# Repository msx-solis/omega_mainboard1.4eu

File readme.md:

# omega_mainboard1.4eu
This is a variant from the OMEGA HOME COMPUTER mainboard pcb 1.4us.
Is based on the last design for the mainboard pcb (version 1.4us). You can find it at https://github.com/skiselev/omega
Please, refer to it for full documentation or you can also go to https://msxmakers.design.blog/proyectos/omega-home-computer/

## changes
The only changes from mainboard version 1.4us are:

a) Din-8 connectors used are more common on EU than in 1.4us version.

b) the jumpers for selecting the mapper changes are not connected so a cutout of the traces is not needed.

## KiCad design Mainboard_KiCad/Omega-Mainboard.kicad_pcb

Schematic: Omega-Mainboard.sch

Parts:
HOLE1, HOLE2, HOLE3, HOLE4, HOLE5, HOLE6, HOLE7, HOLE8, HOLE9, HOLE10, HOLE11: HOLE; Hole_3mm
J1: 5V; Conn_Power_Jack_Circular_Pads
J10: POWER; Conn_Friction_Lock_8P_2.54mm

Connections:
VDD: J10.7; also elsewhere on the board
VSS: J10.8; also elsewhere on the board

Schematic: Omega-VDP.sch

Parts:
C51, C52, C53, C54, C55, C56: 0.1uF; Cap_Cer_508
C59, C60, C61, C62, C63, C64: 220uF; Cap_Elec_Radial_10mm
C77: 10uF; Cap_Elec_Radial_5mm
C82, C83, C84: 330pF; Cap_Cer_508
C85: 47pF; Cap_Cer_508
C89, C90: 30pF; C_Trim_Murata
C91: 27pF; Cap_Cer_508
C92, C93: 22pF; Cap_Cer_508
C94: 4.7pF; Cap_Cer_508
J2: Composite; Conn_RCA_Right
J4: S-VIDEO; Conn_Mini_DIN_4pin
J5: RGB; DIN8
J14: CBUS; Conn_Pin_Header_13x1_2.54mm
JP3, JP4: V9938/V9958; Conn_Pin_Header_3x1_2.54mm
JP5, JP6: NTSC/PAL; Conn_Pin_Header_3x1_2.54mm
L1: 68uH; Res_762
Q2: PN2907A; Transistor_TO92_EBC_254
R1: 1M; Res_762
R2: 470k; Res_762
R7: 47k; Res_762
R9: 20k; Res_762
R14: 10k; Res_762
R25: 2.2k; Res_762
R27, R28, R30, R33: 1k; Res_762
R35: 180; Res_762
R36: 120; Res_762
R37, R38, R39, R40: 100; Res_762
R43, R44, R45, R46, R47, R48: 75; Res_762
RR2, RR3: 10k; Conn_SIL10
RR9: 470; Conn_SIL6
U3: V9938/V9958; IC_SDIP64_600
U8, U9, U10, U11: D41464; IC_DIP18_300
U39: 74AHCT32; IC_DIP14_300
U43: 74HCT04; IC_DIP14_300
U47: CXA1645; IC_DIP24_400
Y1: 21.477270MHz; Crystal_HC-49U_Vert
Y3: 4.433618MHz; Crystal_HC-49U_Vert

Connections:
/A0: U3.29 (MODE0); also elsewhere on the board
/A1: U3.28 (MODE1); also elsewhere on the board
/AUDIO: J5.2; also elsewhere on the board
/CLK: U3.8 (CPUCLK), U39.4, U39.5; also elsewhere on the board
/D0: U3.40 (CD0); also elsewhere on the board
/D1: U3.39 (CD1); also elsewhere on the board
/D2: U3.38 (CD2); also elsewhere on the board
/D3: U3.37 (CD3); also elsewhere on the board
/D4: U3.36 (CD4); also elsewhere on the board
/D5: U3.35 (CD5); also elsewhere on the board
/D6: U3.34 (CD6); also elsewhere on the board
/D7: U3.32 (CD7); also elsewhere on the board
/VDP/AV: J5.3, R14.2, R33.1
/VDP/BLUE: C53.1, C84.1, RR9.6, U3.24 (B)
/VDP/BOUT: C64.2, J5.8
/VDP/CB0: J14.12, RR2.6, U3.19 (C0)
/VDP/CB1: J14.11, RR2.5, U3.18 (C1)
/VDP/CB2: J14.10, RR2.4, U3.17 (C2)
/VDP/CB3: J14.9, RR2.3, U3.16 (C3)
/VDP/CB4: J14.8, RR2.2, U3.15 (C4)
/VDP/CB5: J14.7, RR3.10, U3.14 (C5)
/VDP/CB6: J14.6, RR3.9, U3.13 (C6)
/VDP/CB7: J14.5, RR3.8, U3.12 (C7)
/VDP/CBDR: J14.4, U3.11 (CBDR)
/VDP/CHROMA: C60.2, J4.4
/VDP/COMP: C59.2, J2.1, J5.4
/VDP/CSYNC: R27.2, U3.6 (CSYNC)
/VDP/GOUT: C63.2, J5.7
/VDP/GREEN: C52.1, C83.1, RR9.4, U3.22 (G)
/VDP/HSYNC: RR9.2, U3.5 (HSYNC)
/VDP/LUMA: C61.2, J4.3
/VDP/PAL_CLK: JP6.3, U43.4
/VDP/RED: C51.1, C82.1, RR9.5, U3.23 (R)
/VDP/ROUT: C62.2, J5.6
/VDP/SYNCIN: C85.1, JP4.2, U47.10 (SYNCIN)
/VDP/VA0: U3.49 (AD0), U8.14 (A0), U9.14 (A0), U10.14 (A0), U11.14 (A0)
/VDP/VA1: U3.50 (AD1), U8.13 (A1), U9.13 (A1), U10.13 (A1), U11.13 (A1)
/VDP/VA2: U3.51 (AD2), U8.12 (A2), U9.12 (A2), U10.12 (A2), U11.12 (A2)
/VDP/VA3: U3.52 (AD3), U8.11 (A3), U9.11 (A3), U10.11 (A3), U11.11 (A3)
/VDP/VA4: U3.53 (AD4), U8.8 (A4), U9.8 (A4), U10.8 (A4), U11.8 (A4)
/VDP/VA5: U3.54 (AD5), U8.7 (A5), U9.7 (A5), U10.7 (A5), U11.7 (A5)
/VDP/VA6: U3.55 (AD6), U8.6 (A6), U9.6 (A6), U10.6 (A6), U11.6 (A6)
/VDP/VA7: U3.56 (AD7), U8.10 (A7), U9.10 (A7), U10.10 (A7), U11.10 (A7)
/VDP/VD0: U3.41 (RD0), U8.2 (D1), U10.2 (D1)
/VDP/VD1: U3.42 (RD1), U8.3 (D2), U10.3 (D2)
/VDP/VD2: U3.43 (RD2), U8.15 (D3), U10.15 (D3)
/VDP/VD3: U3.44 (RD3), U8.17 (D4), U10.17 (D4)
/VDP/VD4: U3.45 (RD4), U9.2 (D1), U11.2 (D1)
/VDP/VD5: U3.46 (RD5), U9.3 (D2), U11.3 (D2)
/VDP/VD6: U3.47 (RD6), U9.15 (D3), U11.15 (D3)
/VDP/VD7: U3.48 (RD7), U9.17 (D4), U11.17 (D4)
/VDP/VIDEO: JP3.2, U3.21 (VIDEO)
/VDP/YS: J5.5, R35.2, R36.1
/VDP/~CAS0: R38.1, U8.16 (~CAS), U9.16 (~CAS)
/VDP/~CAS1: R39.1, U10.16 (~CAS), U11.16 (~CAS)
/VDP/~DHCLK: J14.2, RR3.2, U3.2 (~DHCLK)
/VDP/~DLCLK: J14.3, RR3.3, U3.3 (~DLCKL)
/VDP/~RAS: R40.1, U8.5 (~RAS), U9.5 (~RAS), U10.5 (~RAS), U11.5 (~RAS)
/VDP/~VDP_RD: U3.31 (~CSR), U39.3
/VDP/~VDP_WR: U3.30 (~CSW), U39.11
/VDP/~VWR: R37.1, U8.4 (~WE), U9.4 (~WE), U10.4 (~WE), U11.4 (~WE)
/~PSG_CS: U39.9; also elsewhere on the board
/~RD: U39.1; also elsewhere on the board
/~RESET: U3.9 (~RESET); also elsewhere on the board
/~VDP_CS: U39.2, U39.13; also elsewhere on the board
/~VDP_INT: RR2.7, U3.25 (~INT); also elsewhere on the board
/~VDP_WAIT: RR2.8, U3.26 (~LPS); also elsewhere on the board
/~WR: U39.12; also elsewhere on the board
unnamed: C51.2, U47.2 (RIN)
unnamed: C52.2, U47.3 (GIN)
unnamed: C53.2, U47.4 (BIN)
unnamed: C54.1, U47.9 (YCLPC)
unnamed: C55.1, R7.1, U47.13 (IREF)
unnamed: C56.2, U3.33 (VBB)
unnamed: C59.1, R43.1
unnamed: C60.1, R44.1
unnamed: C61.1, R45.1
unnamed: C62.1, R46.1
unnamed: C63.1, R47.1
unnamed: C64.1, R48.1
unnamed: C77.1, U47.14 (VREF)
unnamed: C89.2, R2.2, U3.63 (XTAL1), Y1.2
unnamed: C90.2, R30.1, Y3.2
unnamed: C91.1, U47.17 (YTRAP)
unnamed: C91.2, L1.1
unnamed: C92.2, R2.1, U3.64 (XTAL2), Y1.1
unnamed: C93.2, R1.2, U43.1, Y3.1
unnamed: C94.1, R25.1, U47.6 (SCIN)
unnamed: JP3.1, RR9.3
unnamed: JP4.1, U43.6
unnamed: JP4.3, Q2.2, R27.1
unnamed: JP5.2, U47.7 (NTSC/~PAL)
unnamed: JP6.1, U39.6
unnamed: JP6.2, R25.2
unnamed: Q2.3, R28.2, U43.5
unnamed: R1.1, R30.2, U43.2, U43.3
unnamed: R9.1, U47.18 (FO)
unnamed: R37.2, U3.57 (R/~W)
unnamed: R38.2, U3.61 (~CAS0)
unnamed: R39.2, U3.60 (~CAS1)
unnamed: R40.2, U3.62 (~RAS)
unnamed: R43.2, U47.20 (CVOUT)
unnamed: R44.2, U47.15 (COUT)
unnamed: R45.2, U47.16 (YOUT)
unnamed: R46.2, U47.23 (ROUT)
unnamed: R47.2, U47.22 (GOUT)
unnamed: R48.2, U47.21 (BOUT)
unnamed: RR2.9, U3.27 (~LPD)
unnamed: RR3.4, U3.4 (~VDS)
unnamed: RR3.5, U3.59 (~CASX)
unnamed: RR3.6, U3.7 (BLEO)
unnamed: RR3.7, U3.10 (~YS)
unnamed 387: U39.8; also elsewhere on the board
unnamed 388: U39.10; also elsewhere on the board
VCCRGB: JP5.1, U47.12 (VCC), U47.19 (VCC); also elsewhere on the board
VCCVDP: JP3.3, U3.58 (VCC); also elsewhere on the board

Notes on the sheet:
JP3, JP4: 1-2: V9938; 2-3: V9958 (Use a wire link) JP4, JP5: 1-2: NTSC; 2-3: PAL (Use a wire link)
PAL: R9 - 16k, C91 - 18pF R9 - Tolerance 1%
PCB Layout Notes: Keep trace length between CXA1645 and 75 ohm resistors to minimum CXA1645 bypass capacitors: VCC1(12), VREF(14) -> GND1(1), VCC2(19) -> GND2(24)
Optional: PAL Clock Generator
Optional: RGB Output
Install Q2 only for V9938

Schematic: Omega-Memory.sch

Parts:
J12: RAM_EXT; Conn_Pin_Header_20x2_2.54mm
JP1: ROM_A18; Conn_Pin_Header_2x1_2.54mm
JP7, JP8: RAM_SIZE; Conn_Pin_Header_2x3_2.54mm
R13: 10k; Res_762
RR10: 4.7k; Conn_SIL6
U6: SST39SF040; IC_DIP32_600
U7: AS6C4008; IC_DIP32_600
U15, U16, U17, U18: 74HCT670; IC_DIP16_300
U26: 74F245; IC_DIP20_300
U32: 74AHCT138; IC_DIP16_300
U37: 74AHCT32; IC_DIP14_300

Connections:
/A0: J12.31, U6.12 (A0), U7.12 (A0), U15.5, U15.14, U16.5, U16.14, U17.14, U18.14; also elsewhere on the board
/A1: J12.29, U6.11 (A1), U7.11 (A1), U15.4, U15.13, U16.4, U16.13, U17.13, U18.13; also elsewhere on the board
/A2: J12.27, U6.10 (A2), U7.10 (A2); also elsewhere on the board
/A3: J12.25, U6.9 (A3), U7.9 (A3); also elsewhere on the board
/A4: J12.23, U6.8 (A4), U7.8 (A4); also elsewhere on the board
/A5: J12.21, U6.7 (A5), U7.7 (A5); also elsewhere on the board
/A6: J12.19, U6.6 (A6), U7.6 (A6); also elsewhere on the board
/A7: J12.17, U6.5 (A7), U7.5 (A7); also elsewhere on the board
/A8: J12.20, U6.27 (A8), U7.27 (A8); also elsewhere on the board
/A9: J12.22, U6.26 (A9), U7.26 (A9); also elsewhere on the board
/A10: J12.28, U6.23 (A10), U7.23 (A10); also elsewhere on the board
/A11: J12.24, U6.25 (A11), U7.25 (A11); also elsewhere on the board
/A12: J12.15, U6.4 (A12), U7.4 (A12); also elsewhere on the board
/A13: J12.18, U6.28 (A13), U7.28 (A13); also elsewhere on the board
/A14: U6.29 (A14), U17.5, U18.5; also elsewhere on the board
/A15: U6.3 (A15), U17.4, U18.4; also elsewhere on the board
/D0: U16.3, U16.6, U18.3, U26.9; also elsewhere on the board
/D1: U16.2, U16.7, U18.2, U26.8; also elsewhere on the board
/D2: U16.1, U16.9, U18.1, U26.7; also elsewhere on the board
/D3: U16.10, U16.15, U18.15, U26.6; also elsewhere on the board
/D4: U15.3, U15.6, U17.3, U26.5; also elsewhere on the board
/D5: JP8.5, U15.2, U17.2, U26.4; also elsewhere on the board
/D6: JP8.1, U15.15, U17.15, U26.3; also elsewhere on the board
/D7: JP8.3, U15.1, U17.1, U26.2; also elsewhere on the board
/Memory/MD0: J12.33, U6.13 (DQ0), U7.13 (DQ0), U26.11
/Memory/MD1: J12.35, U6.14 (DQ1), U7.14 (DQ1), U26.12
/Memory/MD2: J12.37, U6.15 (DQ2), U7.15 (DQ2), U26.13
/Memory/MD3: J12.38, U6.17 (DQ3), U7.17 (DQ3), U26.14
/Memory/MD4: J12.36, U6.18 (DQ4), U7.18 (DQ4), U26.15
/Memory/MD5: J12.34, U6.19 (DQ5), U7.19 (DQ5), U26.16
/Memory/MD6: J12.32, U6.20 (DQ6), U7.20 (DQ6), U26.17
/Memory/MD7: J12.30, U6.21 (DQ7), U7.21 (DQ7), U26.18
/Memory/RAM_A14: J12.13, U7.3 (A14), U18.6
/Memory/RAM_A15: J12.12, U7.31 (A15), U18.7
/Memory/RAM_A16: J12.11, U7.2 (A16), U18.9
/Memory/RAM_A17: J12.14, U7.30 (A17), U18.10
/Memory/RAM_A18: J12.9, U7.1 (A18), U17.6
/Memory/RAM_A19: JP7.2, U17.7
/Memory/RAM_A20: JP7.4, U17.10
/Memory/RAM_A21: JP7.6, U17.9
/Memory/ROM_A18: JP1.2, R13.1, U6.1 (A18)
/Memory/~PAGE_RD: U15.11, U16.11, U37.3
/Memory/~PAGE_WR: U15.12, U16.12, U17.12, U18.12, U37.11
/Memory/~RAM0_CS: U7.22 (~CE), U32.15
/Memory/~RAM1_CS: J12.4, U32.14
/Memory/~RAM2_CS: J12.3, U32.13
/Memory/~RAM3_CS: J12.6, U32.12
/Memory/~RAM4_CS: J12.5, U32.11
/Memory/~RAM5_CS: J12.8, U32.10
/Memory/~RAM6_CS: J12.7, U32.9
/Memory/~RAM7_CS: J12.10, U32.7
/ROM_A16: U6.2 (A16); also elsewhere on the board
/ROM_A17: U6.30 (A17); also elsewhere on the board
/~MEM_RD: U26.1; also elsewhere on the board
/~PAGE_CS: U37.2, U37.12; also elsewhere on the board
/~RAM_SL: U32.4, U32.5; also elsewhere on the board
/~RD: J12.26, U6.24 (~OE), U7.24 (~OE), U37.1; also elsewhere on the board
/~ROM_CS: U6.22 (~CE); also elsewhere on the board
/~WR: J12.16, U6.31 (~WE), U7.29 (~WE), U37.13; also elsewhere on the board
unnamed: JP7.1, RR10.2, U32.1
unnamed: JP7.3, RR10.3, U32.2
unnamed: JP7.5, RR10.4, U32.3
unnamed: JP8.2, U15.10
unnamed: JP8.4, U15.9
unnamed: JP8.6, U15.7

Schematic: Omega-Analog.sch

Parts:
C1, C2, C3, C4, C6, C7, C8, C9, C10, C11, C12, C13, C14, C15, C16, C17, C18, C19, C20, C21, C22, C23, C24, C25, C26, C27, C28, C29, C30, C31, C32, C33, C34, C35, C36, C37, C38, C39, C40, C41, C42, C43, C44, C45, C46, C47, C48, C49, C50, C57, C58: 0.1uF; Cap_Cer_508
C65, C66, C67: 100uF; Cap_Elec_Radial_6.3mm
C68, C69, C70: 10uF; Cap_Pol_508_3
C71, C72, C73, C74, C75, C76: 10uF; Cap_Elec_Radial_5mm
C78: 1uF; Cap_Elec_Radial_5mm
C79, C80: 22nF; Cap_Cer_508
C81: 1.5nF; Cap_Cer_508
D1: 1N4148; Diode_762
J3: Audio; Conn_RCA_Right
J6: Cassette; DIN8
L2, L3: 5.6uH; Res_762
Q1: PN2907A; Transistor_TO92_EBC_254
R3: 470k; Res_762
R4: 220k; Res_762
R8: 47k; Res_762
R10: 20k; Res_762
R11, R12: 10k; Res_762
R15: 5.6k; Res_762
R16, R17, R18, R19, R20, R21, R22: 4.7k; Res_762
R23, R24: 2.7k; Res_762
R26: 2.2k; Res_762
R31, R32: 1k; Res_762
R41, R42: 100; Res_762
RY1: Relay_5V; Relay_SPDT
U48: MCP6281; IC_DIP8_300
U49: LM311; IC_DIP8_300

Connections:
/AUDIO: C76.2, J3.1, R8.1; also elsewhere on the board
/CAS_IN: R4.2, R32.1, U49.7; also elsewhere on the board
/CAS_MOT: R31.1; also elsewhere on the board
/CAS_OUT: C78.1; also elsewhere on the board
/KEY_CLICK: C73.1; also elsewhere on the board
/PSG_SND: C72.1; also elsewhere on the board
/SLT1_SND: C74.1; also elsewhere on the board
/SLT2_SND: C75.1; also elsewhere on the board
unnamed: C57.1, R21.1, R22.2, U48.3
unnamed: C71.1, R12.2, R20.1, R23.1, R24.1
unnamed: C72.2, R26.2
unnamed: C73.2, R10.2
unnamed: C74.2, R16.2
unnamed: C75.2, R17.2
unnamed: C76.1, R41.2
unnamed: C78.2, R18.1
unnamed: C79.1, R18.2, R19.1
unnamed: C80.1, J6.5
unnamed: C80.2, R11.2
unnamed: C81.1, R10.1, R15.1, R16.1, R17.1, R26.1, U48.2
unnamed: C81.2, R15.2, R41.1, U48.6
unnamed: D1.2, Q1.1, RY1.9
unnamed: J6.4, R19.2, R42.1
unnamed: J6.6, RY1.5, RY1.6
unnamed: J6.7, RY1.10
unnamed: Q1.2, R31.2
unnamed: R3.2, R11.1, R12.1, U49.3 (-)
unnamed: R4.1, R20.2, U49.2 (+)
VCCRGB: C47.1, C50.1, C69.1, L3.2; also elsewhere on the board
VCCVDP: C3.1, C58.1, C70.1, L2.2; also elsewhere on the board
VDD: C66.1; also elsewhere on the board
VSS: C67.2; also elsewhere on the board

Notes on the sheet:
C5: RTC
Optional: Cassete I/O

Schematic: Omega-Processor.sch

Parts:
BT1: CR2032; Battery_Holder_CR2032_Universal
C5: 0.1uF; Cap_Cer_508
C86, C87: 33pF; Cap_Cer_508
C88: 30pF; C_Trim_Murata
J9: PRINTER; Conn_Micro_Ribbon_14F
J13: ~RST~/~NMI; Conn_Pin_Header_2x2_2.54mm
R5, R6: 100k; Res_762
R29: 1k; Res_762
RR1: 10k; Conn_SIL10
RR5: 4.7k; Conn_SIL10
U1: Z84C00; IC_DIP40_600
U5: RP5C01; IC_DIP18_300
U12: ATF16V8B; IC_DIP20_300
U24: 74HCT273; IC_DIP20_300
U27: 74HCT175; IC_DIP16_300
U33: 74AHCT125; IC_DIP14_300
U34, U35: 74HCT74; IC_DIP14_300
U37: 74AHCT32; IC_DIP14_300
U42: 74LS07; IC_DIP14_300
U45: 74HCT00; IC_DIP14_300
U46: ADM691A; IC_DIP16_300
Y2: 32768 Hz; Crystal_32K_Horiz

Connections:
/A0: U1.30 (A0), U12.9 (I8); also elsewhere on the board
/A1: U1.31 (A1); also elsewhere on the board
/A2: U1.32 (A2), U12.8 (I7); also elsewhere on the board
/A3: U1.33 (A3), U12.7 (I6); also elsewhere on the board
/A4: U1.34 (A4), U12.6 (I5); also elsewhere on the board
/A5: U1.35 (A5), U12.5 (I4); also elsewhere on the board
/A6: U1.36 (A6), U12.4 (I3); also elsewhere on the board
/A7: U1.37 (A7), U12.3 (I2); also elsewhere on the board
/A8: U1.38 (A8); also elsewhere on the board
/A9: U1.39 (A9); also elsewhere on the board
/A10: U1.40 (A10); also elsewhere on the board
/A11: U1.1 (A11); also elsewhere on the board
/A12: U1.2 (A12); also elsewhere on the board
/A13: U1.3 (A13); also elsewhere on the board
/A14: U1.4 (A14); also elsewhere on the board
/A15: U1.5 (A15); also elsewhere on the board
/CLK: U35.11 (CLK), U42.5, U42.9; also elsewhere on the board
/D0: RR1.3, U1.14 (D0), U5.11 (D0), U24.17 (D6), U27.5 (D1), U35.2 (D); also elsewhere on the board
/D1: RR1.4, U1.15 (D1), U5.12 (D1), U24.14 (D5), U27.4 (D0), U33.3; also elsewhere on the board
/D2: RR1.5, U1.12 (D2), U5.13 (D2), U24.4 (D1), U27.12 (D2); also elsewhere on the board
/D3: RR1.6, U1.8 (D3), U5.14 (D3), U24.7 (D2), U27.13 (D3); also elsewhere on the board
/D4: RR1.7, U1.7 (D4), U24.13 (D4); also elsewhere on the board
/D5: RR1.8, U1.9 (D5), U24.8 (D3); also elsewhere on the board
/D6: RR1.9, U1.10 (D6), U24.18 (D7); also elsewhere on the board
/D7: RR1.10, U1.13 (D7), U24.3 (D0); also elsewhere on the board
/PRT_BUSY: J9.11, U33.2; also elsewhere on the board
/PSG/JB0: U42.1; also elsewhere on the board
/PSG/JB1: U42.13; also elsewhere on the board
/PSG/JB2: U42.11; also elsewhere on the board
/PSG/JB3: U42.3; also elsewhere on the board
/PSG/~TRG1_A: U42.2; also elsewhere on the board
/PSG/~TRG1_B: U42.12; also elsewhere on the board
/PSG/~TRG2_A: U42.10; also elsewhere on the board
/PSG/~TRG2_B: U42.4; also elsewhere on the board
/Processor/ALARM: RR1.2, U5.15 (~ALARM)
/Processor/PD0: J9.2, U24.16 (Q6)
/Processor/PD1: J9.3, U24.15 (Q5)
/Processor/PD2: J9.4, U24.5 (Q1)
/Processor/PD3: J9.5, U24.6 (Q2)
/Processor/PD4: J9.6, U24.12 (Q4)
/Processor/PD5: J9.7, U24.9 (Q3)
/Processor/PD6: J9.8, U24.19 (Q7)
/Processor/PD7: J9.9, U24.2 (Q0)
/Processor/RTC_VCC: C5.1, U5.2 (CS), U5.18 (VCC), U46.2 (Vout)
/Processor/~BUSREQ: RR5.3, U1.25 (~BUSREQ)
/Processor/~INT: U1.16 (~INT), U45.8
/Processor/~NMI: J13.3, RR5.4, U1.17 (~NMI)
/Processor/~PRT_BSY_RD: U33.1, U37.6
/Processor/~PRT_CMD_CS: U12.13 (I/O7), U37.5, U37.10
/Processor/~PRT_DAT_WR: U12.12 (I/O8), U24.11 (CP)
/Processor/~PRT_STB_WR: U35.3 (CLK), U37.8
/Processor/~RTC_AD_WR: U12.17 (I/O3), U27.9 (CP)
/Processor/~RTC_CS: U12.16 (I/O4), U46.13 (~CE_IN)
/Processor/~RTC_CS_B: U5.1 (~CS), U46.12 (~CE_OUT)
/Processor/~STROBE: J9.1, U35.5 (Q)
/RESET: U46.16 (RESET); also elsewhere on the board
/~BUSDIR1: RR5.7; also elsewhere on the board
/~BUSDIR2: RR5.6; also elsewhere on the board
/~IORQ: U1.20 (~IORQ), U12.2 (I1); also elsewhere on the board
/~KBD_WAIT: RR5.2; also elsewhere on the board
/~M1: U1.27 (~M1), U12.11 (I9/~OE), U34.2 (D); also elsewhere on the board
/~M1_WAIT: U34.5 (Q), U34.12 (D); also elsewhere on the board
/~MREQ: U1.19 (~MREQ); also elsewhere on the board
/~PAGE_CS: U12.15 (I/O5); also elsewhere on the board
/~PPI_CS: U12.14 (I/O6), U45.4; also elsewhere on the board
/~PSG_CS: U12.19 (I/O1); also elsewhere on the board
/~RD: U1.21 (~RD), U5.8 (~RD), U37.4; also elsewhere on the board
/~RESET: J13.1, U1.26 (~RESET), U24.1 (~MR), U27.1 (~MR), U35.4 (~PR), U45.2, U46.15 (~RESET); also elsewhere on the board
/~RFSH: U1.28 (~RFSH); also elsewhere on the board
/~SLT_INT: RR5.9, U45.13; also elsewhere on the board
/~SLT_WAIT: RR5.10; also elsewhere on the board
/~VDP_CS: U12.18 (I/O2); also elsewhere on the board
/~VDP_INT: U45.12; also elsewhere on the board
/~WAIT: U1.24 (~WAIT); also elsewhere on the board
/~WR: U1.22 (~WR), U5.10 (~WR), U12.1 (I/CLK), U37.9; also elsewhere on the board
unnamed: BT1.1, U46.1 (Vbatt)
unnamed: C86.2, R5.1, U5.17 (OSCOUT)
unnamed: C87.2, R5.2, Y2.2
unnamed: C88.2, U5.16 (OSCIN), Y2.1
unnamed: R6.1, U5.3 (ADJ)
unnamed: R29.2, U1.6 (CLK), U34.3 (CLK), U34.11 (CLK), U42.8
unnamed 330: U42.6; also elsewhere on the board
unnamed: U5.5 (A1), U27.2 (Q0)
unnamed: U5.4 (A0), U27.7 (Q1)
unnamed: U5.6 (A2), U27.10 (Q2)
unnamed: U5.7 (A3), U27.15 (Q3)
unnamed 370: U45.3, U45.5; also elsewhere on the board
unnamed: U34.4 (~PR), U34.9 (Q)
unnamed 378: U35.9 (Q); also elsewhere on the board
unnamed: U35.8 (~Q), U35.12 (D)
unnamed: U45.1, U45.6
unnamed: U45.9, U45.10, U45.11

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
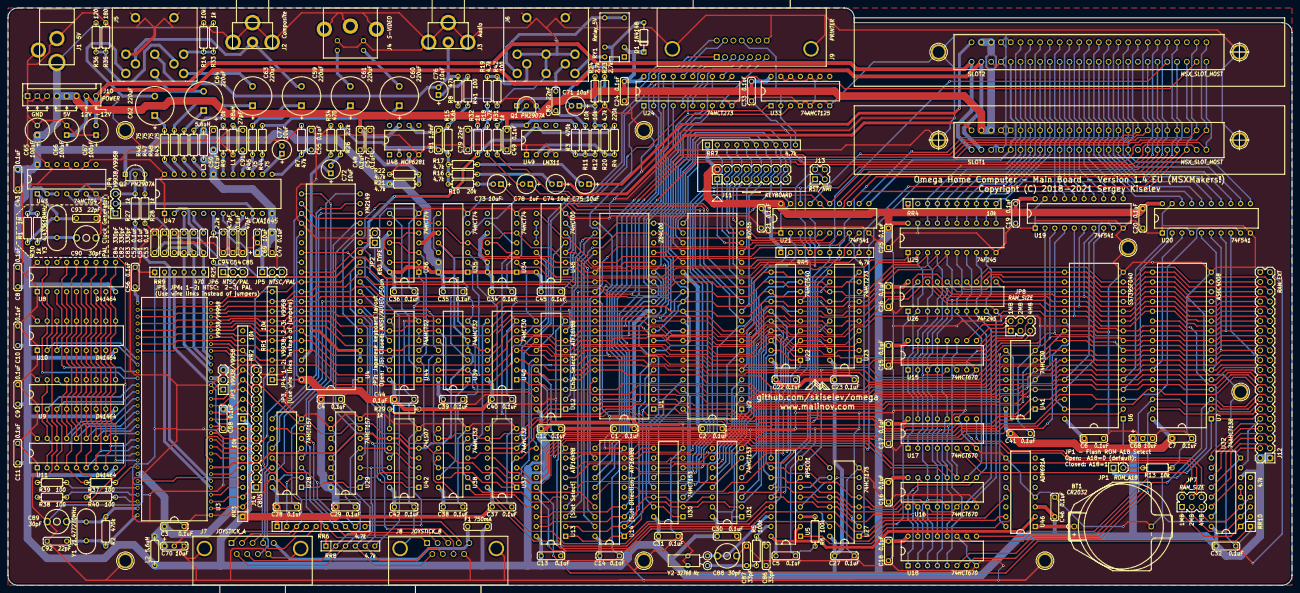
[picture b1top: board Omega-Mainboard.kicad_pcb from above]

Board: 2 copper layers, 333.4 x 149.9 mm, 248 parts (0 on the bottom side), 363 nets.

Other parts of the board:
F1: 750mA; Cap_Cer_508
J7: JOYSTICK_A; Conn_Dsub_DE9M
J8: JOYSTICK_B; Conn_Dsub_DE9M
J11: KEYBOARD; Conn_Pin_Header_8x2_2.54mm
JP2: KBD_TYPE; Conn_Pin_Header_2x1_2.54mm
R34: 470; Res_762
RR4: 10k; Conn_SIL10
RR6, RR7: 4.7k; Conn_SIL10
RR8: 4.7k; Conn_SIL6
SLOT1, SLOT2: MSX_SLOT_HOST; Conn_Edge_50P
U2: 82C55; IC_DIP40_600
U4: YM2149; IC_DIP40_600
U13, U14: ATF16V8B; IC_DIP20_300
U19, U20, U21: 74F541; IC_DIP20_300
U22: 74HCT540; IC_DIP20_300
U23: 74HCT273; IC_DIP20_300
U25: 74F245; IC_DIP20_300
U28, U29: 74HCT157; IC_DIP16_300
U30, U31: 74HCT153; IC_DIP16_300
U36: 74HCT74; IC_DIP14_300
U38: 74AHCT32; IC_DIP14_300
U40, U41: 74HCT30; IC_DIP14_300
U44: 74AHCT02; IC_DIP14_300

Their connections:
/A0: U2.9, U19.7, U40.12, U44.9; also elsewhere on the board
/A1: U2.8, U19.6, U40.11, U44.11; also elsewhere on the board
/A2: U19.5, U40.6; also elsewhere on the board
/A3: U19.4, U40.5; also elsewhere on the board
/A4: U19.3, U40.4; also elsewhere on the board
/A5: U19.2, U40.3; also elsewhere on the board
/A6: U20.5, U40.2; also elsewhere on the board
/A7: U20.4, U40.1; also elsewhere on the board
/A8: U20.3, U41.11; also elsewhere on the board
/A9: U20.8, U41.5; also elsewhere on the board
/A10: U20.7, U41.4; also elsewhere on the board
/A11: U20.6, U41.6; also elsewhere on the board
/A12: U20.2, U41.3; also elsewhere on the board
/A13: U19.9, U41.12; also elsewhere on the board
/A14: U13.2, U14.2, U19.8, U30.14, U31.14, U41.2; also elsewhere on the board
/A15: U13.1, U14.1, U20.9, U30.2, U31.2, U41.1; also elsewhere on the board
/CAS_IN: U4.14; also elsewhere on the board
/CAS_MOT: U2.13; also elsewhere on the board
/CAS_OUT: U2.12; also elsewhere on the board
/CLK: U21.9; also elsewhere on the board
/D0: U2.34, U4.37, U22.18, U23.3, U25.9; also elsewhere on the board
/D1: U2.33, U4.36, U22.17, U23.18, U25.8; also elsewhere on the board
/D2: U2.32, U4.35, U22.16, U23.17, U25.7; also elsewhere on the board
/D3: U2.31, U4.34, U22.15, U23.4, U25.6; also elsewhere on the board
/D4: U2.30, U4.33, U22.14, U23.7, U25.5; also elsewhere on the board
/D5: U2.29, U4.32, U22.13, U23.14, U25.4; also elsewhere on the board
/D6: U2.28, U4.31, U22.12, U23.13, U25.3; also elsewhere on the board
/D7: U2.27, U4.30, U22.11, U23.8, U25.2; also elsewhere on the board
/KANA_LED: J11.14, U4.6
/KEY_CLICK: U2.10; also elsewhere on the board
/PPI/CAPS_LED: J11.12, U2.11
/PPI/COLUMN0: J11.1, RR7.2, U2.18
/PPI/COLUMN1: J11.3, RR7.3, U2.19
/PPI/COLUMN2: J11.5, RR7.4, U2.20
/PPI/COLUMN3: J11.7, RR7.5, U2.21
/PPI/COLUMN4: J11.9, RR7.6, U2.22
/PPI/COLUMN5: J11.11, RR7.7, U2.23
/PPI/COLUMN6: J11.13, RR7.8, U2.24
/PPI/COLUMN7: J11.15, RR7.9, U2.25
/PPI/ROW_A: J11.4, U2.14
/PPI/ROW_B: J11.6, U2.15
/PPI/ROW_C: J11.8, U2.16
/PPI/ROW_D: J11.10, U2.17
/PPI/SB_SLT_A: U13.6, U31.7
/PPI/SB_SLT_B: U13.7, U31.9
/PPI/SLT_A: U13.8, U30.7
/PPI/SLT_B: U13.9, U30.9
/PPI/~FFFF: U13.5, U38.2, U38.6
/PPI/~SLTSL3: U13.17, U38.1
/PPI/~SUB_RD: U22.1, U22.19, U38.11
/PPI/~SUB_REG_CS: U38.3, U38.10, U38.12
/PPI/~SUB_WR: U23.11, U38.8
/PRT_BUSY: RR7.10; also elsewhere on the board
/PSG/JB0: U4.13; also elsewhere on the board
/PSG/JB1: U4.12; also elsewhere on the board
/PSG/JB2: U4.11; also elsewhere on the board
/PSG/JB3: U4.10; also elsewhere on the board
/PSG/JOY_BCK: U4.20, U28.7
/PSG/JOY_FWD: U4.21, U28.4
/PSG/JOY_LFT: U4.19, U28.9
/PSG/JOY_OUT_A: J7.8, U4.9
/PSG/JOY_OUT_B: J8.8, U4.8
/PSG/JOY_RGT: U4.18, U28.12
/PSG/JOY_SEL: U4.7, U28.1, U29.1
/PSG/JOY_TRG1: U4.17, U29.4
/PSG/JOY_TRG2: U4.16, U29.7
/PSG/KBD_TYPE: JP2.1, RR8.6, U4.15
/PSG/PSG_BC1: U4.29, U44.10
/PSG/PSG_BDIR: U4.27, U44.13
/PSG/~BCK_A: J7.2, RR6.3, U28.5
/PSG/~BCK_B: J8.2, RR6.7, U28.6
/PSG/~FWD_A: J7.1, RR6.2, U28.2
/PSG/~FWD_B: J8.1, RR6.6, U28.3
/PSG/~LFT_A: J7.3, RR6.4, U28.11
/PSG/~LFT_B: J8.3, RR6.8, U28.10
/PSG/~RGT_A: J7.4, RR6.5, U28.14
/PSG/~RGT_B: J8.4, RR6.9, U28.13
/PSG/~TRG1_A: J7.6, RR8.3, U29.2; also elsewhere on the board
/PSG/~TRG1_B: J8.6, RR8.4, U29.3; also elsewhere on the board
/PSG/~TRG2_A: J7.7, RR8.2, U29.5; also elsewhere on the board
/PSG/~TRG2_B: J8.7, RR8.5, U29.6; also elsewhere on the board
/PSG_SND: R34.1, U4.3, U4.4, U4.38; also elsewhere on the board
/RESET: U2.35; also elsewhere on the board
/ROM_A16: U13.13; also elsewhere on the board
/ROM_A17: U13.12; also elsewhere on the board
/SLT1_SND: SLOT1.49; also elsewhere on the board
/SLT2_SND: SLOT2.49; also elsewhere on the board
/Slots/BA0: SLOT1.28, SLOT2.28, U19.13
/Slots/BA1: SLOT1.27, SLOT2.27, U19.14
/Slots/BA2: SLOT1.30, SLOT2.30, U19.15
/Slots/BA3: SLOT1.29, SLOT2.29, U19.16
/Slots/BA4: SLOT1.32, SLOT2.32, U19.17
/Slots/BA5: SLOT1.31, SLOT2.31, U19.18
/Slots/BA6: SLOT1.22, SLOT2.22, U20.15
/Slots/BA7: SLOT1.21, SLOT2.21, U20.16
/Slots/BA8: SLOT1.24, SLOT2.24, U20.17
/Slots/BA9: SLOT1.17, SLOT2.17, U20.12
/Slots/BA10: SLOT1.20, SLOT2.20, U20.13
/Slots/BA11: SLOT1.19, SLOT2.19, U20.14
/Slots/BA12: SLOT1.23, SLOT2.23, U20.18
/Slots/BA13: SLOT1.26, SLOT2.26, U19.11
/Slots/BA14: SLOT1.25, SLOT2.25, U19.12
/Slots/BA15: SLOT1.18, SLOT2.18, U20.11
/Slots/BD0: RR4.10, SLOT1.34, SLOT2.34, U25.11
/Slots/BD1: RR4.9, SLOT1.33, SLOT2.33, U25.12
/Slots/BD2: RR4.8, SLOT1.36, SLOT2.36, U25.13
/Slots/BD3: RR4.7, SLOT1.35, SLOT2.35, U25.14
/Slots/BD4: RR4.6, SLOT1.38, SLOT2.38, U25.15
/Slots/BD5: RR4.5, SLOT1.37, SLOT2.37, U25.16
/Slots/BD6: RR4.4, SLOT1.40, SLOT2.40, U25.17
/Slots/BD7: RR4.3, SLOT1.39, SLOT2.39, U25.18
/Slots/B_CLK: SLOT1.42, SLOT2.42, U21.11
/Slots/SLT_DIR: U14.12, U25.1
/Slots/~B_IORQ: SLOT1.11, SLOT2.11, U14.8, U21.15
/Slots/~B_M1: SLOT1.9, SLOT2.9, U14.7, U21.16
/Slots/~B_MREQ: SLOT1.12, SLOT2.12, U21.14
/Slots/~B_RD: SLOT1.14, SLOT2.14, U14.9, U21.18
/Slots/~B_RESET: SLOT1.15, SLOT2.15, U21.12
/Slots/~B_RFSH: SLOT1.6, SLOT2.6, U21.13
/Slots/~B_WR: SLOT1.13, SLOT2.13, U21.17
/Slots/~CS1: SLOT1.1, SLOT2.1, U14.14
/Slots/~CS2: SLOT1.2, SLOT2.2, U14.15
/Slots/~CS12: SLOT1.3, SLOT2.3, U14.13
/~BUSDIR1: SLOT1.10, U14.5; also elsewhere on the board
/~BUSDIR2: SLOT2.10, U14.6; also elsewhere on the board
/~IORQ: U21.5; also elsewhere on the board
/~KBD_WAIT: U14.16; also elsewhere on the board
/~M1: U21.4; also elsewhere on the board
/~M1_WAIT: U14.18; also elsewhere on the board
/~MEM_RD: U13.16; also elsewhere on the board
/~MREQ: U13.3, U21.6; also elsewhere on the board
/~PPI_CS: U2.6; also elsewhere on the board
/~PSG_CS: U44.5, U44.6; also elsewhere on the board
/~RAM_SL: U13.15; also elsewhere on the board
/~RD: U2.5, U13.11, U21.2, U38.13; also elsewhere on the board
/~RESET: U4.23, U21.8, U23.1; also elsewhere on the board
/~RFSH: U13.4, U21.7; also elsewhere on the board
/~ROM_CS: U13.14; also elsewhere on the board
/~SLTSL1: SLOT1.4, U13.19, U14.3
/~SLTSL2: SLOT2.4, U13.18, U14.4
/~SLT_INT: SLOT1.8, SLOT2.8; also elsewhere on the board
/~SLT_WAIT: SLOT1.7, SLOT2.7, U14.11; also elsewhere on the board
/~VDP_WAIT: U14.17; also elsewhere on the board
/~WAIT: U14.19; also elsewhere on the board
/~WR: U2.36, U21.3, U38.9; also elsewhere on the board
unnamed: F1.1, J7.5, J8.5
unnamed 330: RR6.10, U36.3, U36.11, U44.3; also elsewhere on the board
unnamed: U2.1, U30.11
unnamed: U2.2, U30.5
unnamed: U2.3, U30.10
unnamed: U2.4, U30.6
unnamed: U2.37, U30.13
unnamed: U2.38, U30.3
unnamed: U2.39, U30.12
unnamed: U2.40, U30.4
unnamed: U22.2, U23.2, U31.6
unnamed: U22.3, U23.19, U31.10
unnamed: U22.4, U23.16, U31.5
unnamed: U22.5, U23.5, U31.11
unnamed: U22.6, U23.6, U31.4
unnamed: U22.7, U23.15, U31.12
unnamed: U22.8, U23.12, U31.3
unnamed: U22.9, U23.9, U31.13
unnamed 370: U30.1, U30.15; also elsewhere on the board
unnamed 378: U4.22; also elsewhere on the board
unnamed: U36.1, U36.2, U36.13, U44.4
unnamed: U36.8, U44.2
unnamed: U36.5, U36.12
unnamed: U38.4, U41.8
unnamed: U38.5, U40.8
unnamed 387: U44.8, U44.12; also elsewhere on the board
unnamed 388: U44.1; also elsewhere on the board
VDD: SLOT1.48, SLOT2.48; also elsewhere on the board
VSS: SLOT1.50, SLOT2.50; also elsewhere on the board

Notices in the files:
Mainboard_KiCad/Omega-Mainboard.kicad_pcb:
Copyright (C) 2018-2021 Sergey Kiselev
